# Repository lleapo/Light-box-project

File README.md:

# Light-box-project

Design Skills Project (Variable Light Intensity)
Functional Specifications
LED light that is button-activated to switch between the following operating modes:
Off
Brightest
Intermediate Brightness
Least Bright
Flashing @ 2 Hz
Self-contained device with LED and button exposed.
Extra credit possibilities:
Battery life indicator
Waterproof enclosure
You tell us!
Constraints
Run on single battery up to 9 V
Electronics connected to a single PCB (can be single- or double-sided)
Cannot weight more than 1 lb
Cannot have a single dimension > 6 in
Cannot cost more than $50 to duplicate unit
Battery must be easily replaceable
Evaluation
Minimize weight

Minimize size

Maximize Brightest mode

Minimize power draw / maximize battery life

Survive 3 foot drop with battery installed

Create-and-maintain a GitHub project repository to maintain version history of:

Mechanical CAD (PDFs + more)
Electronic CAD (PDFs + more)
Software
Testing data
Design history / notes
Specification sheets
Usage notes (README.md)
Kanban board / Issues / Milestones

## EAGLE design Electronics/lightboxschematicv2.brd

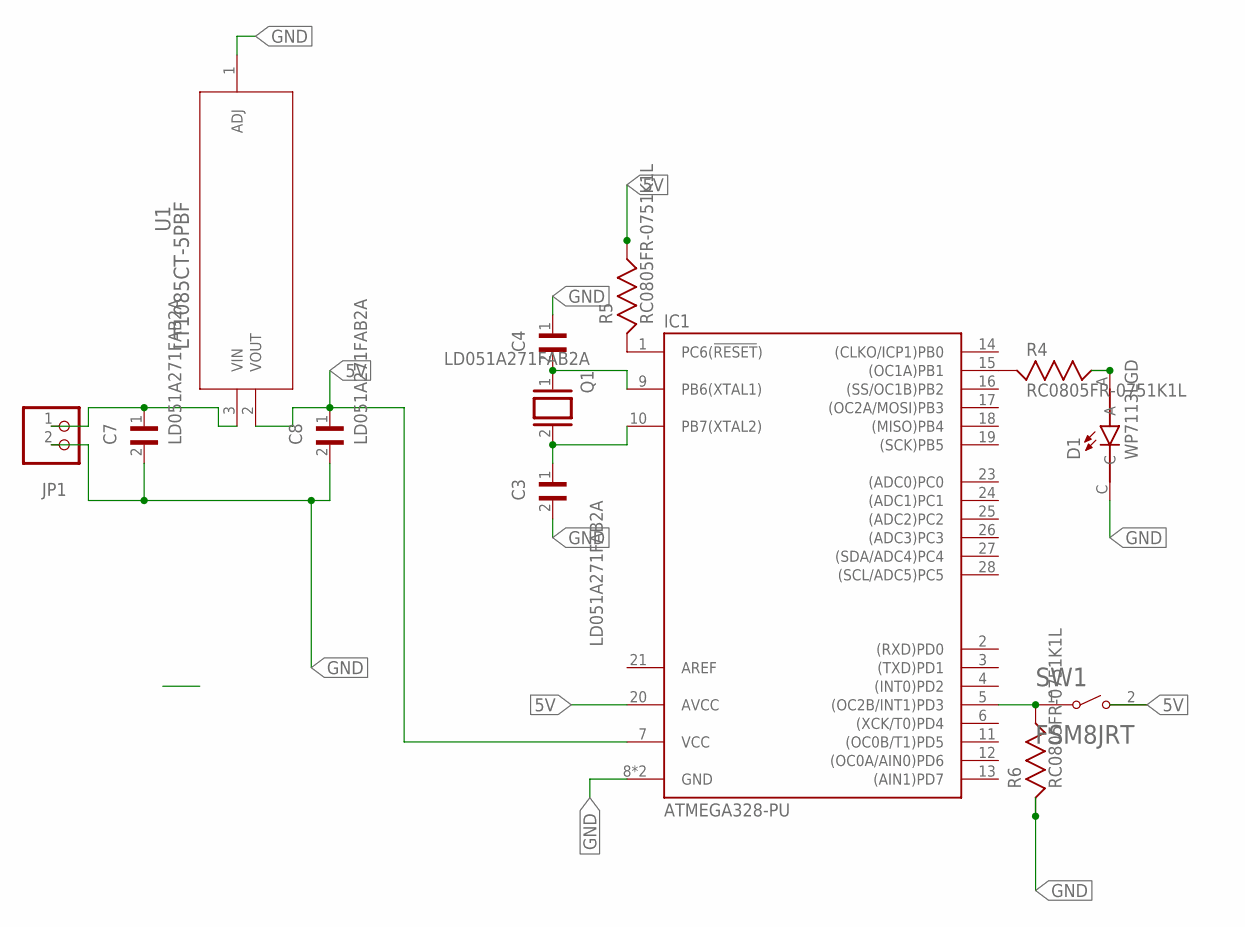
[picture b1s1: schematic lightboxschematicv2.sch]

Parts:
C3, C4, C7, C8: LD051A271FAB2A; CAPC2012X140N
D1: WP7113LGD; LED_WP7113LGD
IC1: ATMEGA328-PU; DIL28
JP1: PINHD-1X2; 1X02
Q1: XTAL/S; QS
R4, R5, R6: RC0805FR-0751K1L; RESC2012X60
SW1: FSM8JRT; TE_FSM8JRT
U1: LT1085CT-5PBF; TO220-3_T

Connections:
5V: C8.1, IC1.7 (VCC), IC1.20 (AVCC), R5.2, SW1.2, U1.2 (VOUT)
GND: C3.2, C4.1, C7.2, C8.2, D1.C, IC1.8 (GND), IC1.11 ((OC0B/T1)PD5), IC1.22 (GND), JP1.2, R6.1, U1.1 (ADJ)
unnamed: IC1.1 (PC6(!RESET!)), R5.1
unnamed: D1.A, R4.2
unnamed: C7.1, JP1.1, U1.3 (VIN)
unnamed: IC1.5 ((OC2B/INT1)PD3), R6.2, SW1.1
unnamed: IC1.15 ((OC1A)PB1), R4.1
unnamed: C4.2, IC1.9 (PB6(XTAL1)), Q1.1
unnamed: C3.1, IC1.10 (PB7(XTAL2)), Q1.2

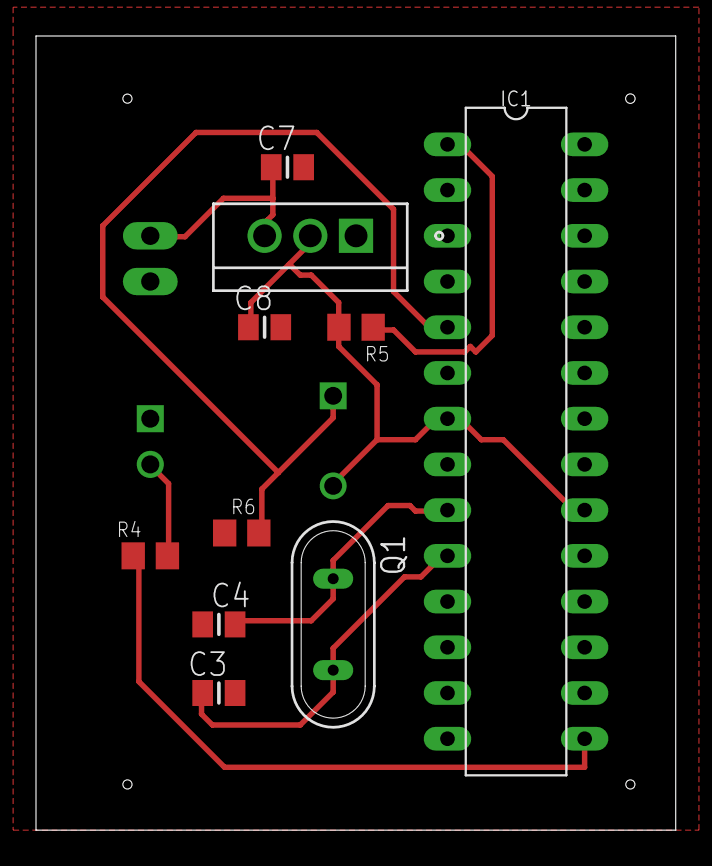
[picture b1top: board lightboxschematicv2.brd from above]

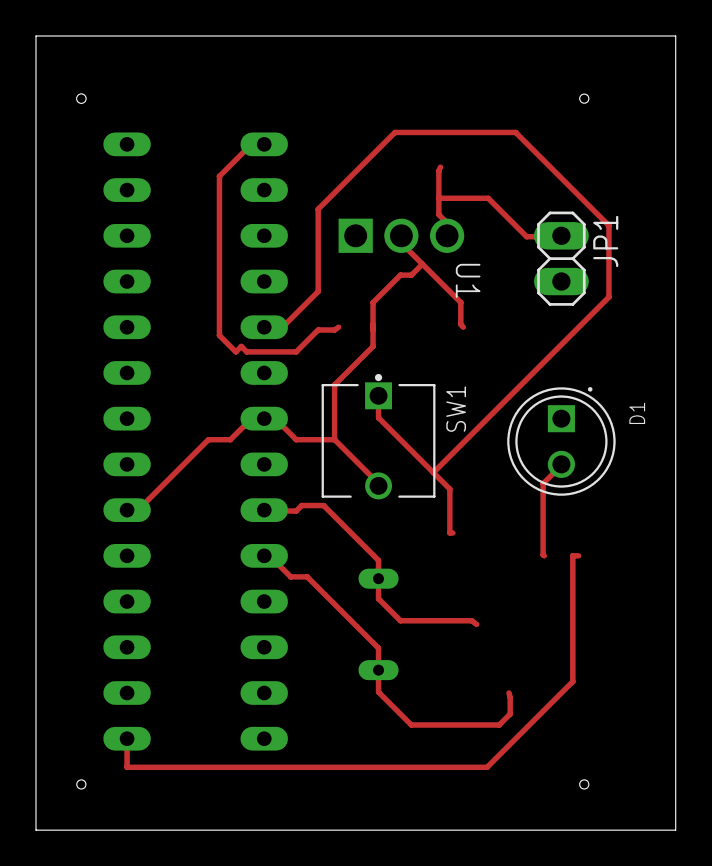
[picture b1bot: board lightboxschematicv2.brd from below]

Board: 2 copper layers, 35.5 x 44.1 mm, 13 parts (3 on the bottom side), 9 nets.

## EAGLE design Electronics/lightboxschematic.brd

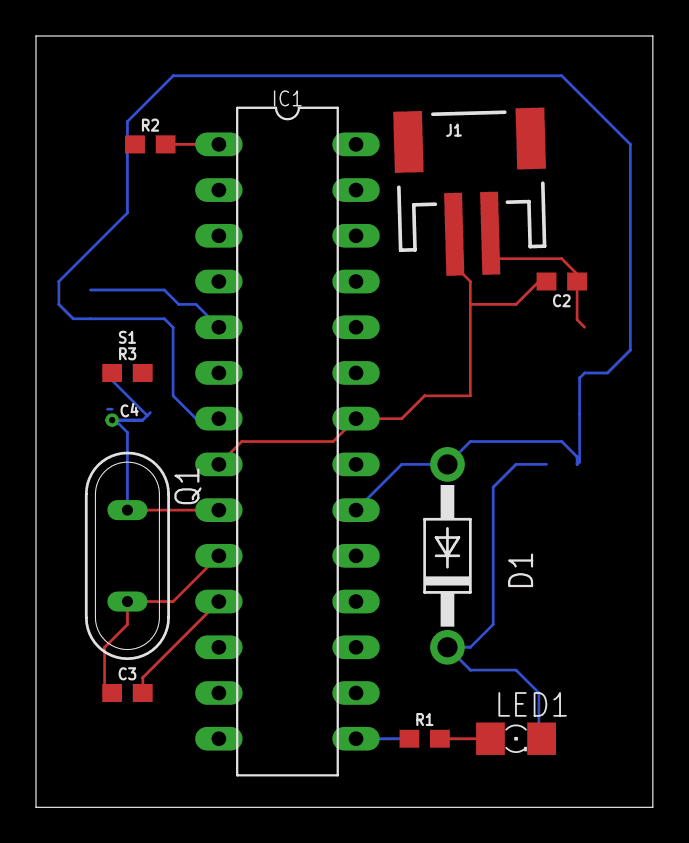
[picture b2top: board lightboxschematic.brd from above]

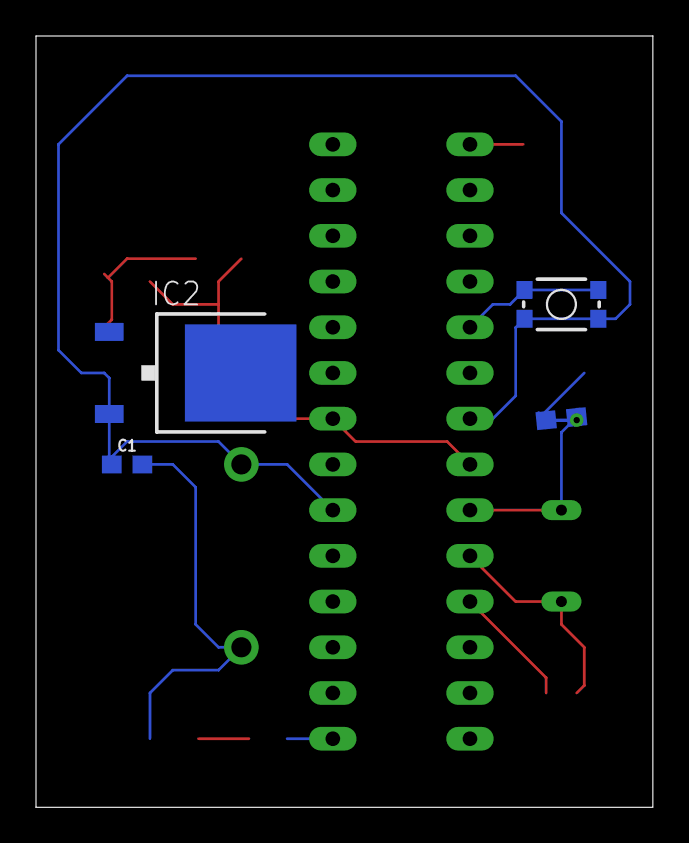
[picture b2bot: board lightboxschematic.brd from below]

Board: 2 copper layers, 34.3 x 42.8 mm, 14 parts (4 on the bottom side), 9 nets.

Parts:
C1, C2: 10uF; 0603
C3, C4: 22pF; 0603
D1: 1N4004; DO41-10
IC1: ATMEGA328-PU; DIL28
IC2: 7808DT; TO252
J1: JST-2-SMD
LED1: 1206
Q1: QS
R1: 150; 0603
R2: 10k; 0603
R3: 100k; 0603
S1: MOMENTARY-SWITCH-SPST-SMD-4.6X2.8MM; TACTILE_SWITCH_SMD_4.6X2.8MM

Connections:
5V: C1.1, D1.A, IC1.7, IC1.20, IC2.2, R2.1, S1.3, S1.4
GND: C1.2, C2.2, C3.2, C4.1, D1.C, IC1.8, IC1.11, IC1.22, IC2.3, J1.1, LED1.C, R3.1
unnamed: IC1.15, R1.1
unnamed: LED1.A, R1.2
unnamed: C2.1, IC2.1, J1.2
unnamed: IC1.5, R3.2, S1.1, S1.2
unnamed: IC1.1, R2.2
unnamed: C4.2, IC1.9, Q1.1
unnamed: C3.1, IC1.10, Q1.2

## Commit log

2018-11-01 Software/ softwareflowchart
2018-11-01 Electronics/ circuitschematic
2018-11-01 circuit schematic
2018-11-01 Create softwareflowchart
2018-11-01 software flow chart
2018-11-01 Add files via upload
    DRAFT of code- done before Tuesday's class, needs to be reorganized
2018-11-08 milestone4 board
2018-11-08 Add files via upload
    milestone 4 blinking light
2018-11-18 Add files via upload
    updated ECAD with ground plane and lab components
2018-11-19 Create CADdesign
2018-11-19 Add files via upload
    the 2D drawing and 3D rendering are labeled lightboxassembly
2018-11-19 Add files via upload
    3D pdf of assembly

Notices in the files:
parts and their libraries:
SparkFun-Capacitors: Licensing: Creative Commons ShareAlike 4.0 International - https://creativecommons.org/licenses/by-sa/4.0
